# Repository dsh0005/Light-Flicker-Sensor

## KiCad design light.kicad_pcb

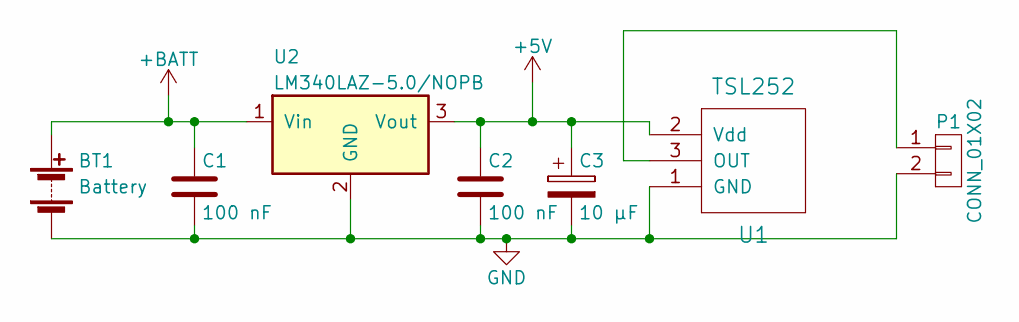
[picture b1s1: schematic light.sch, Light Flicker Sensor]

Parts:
BT1: Battery; TerminalBlock_bornier-2_P5.08mm
C1, C2: 100 nF; C_Disc_D5.0mm_W2.5mm_P5.00mm
C3: 10 µF; CP_Radial_Tantal_D5.0mm_P5.00mm
P1: CONN_01X02; TerminalBlock_bornier-2_P5.08mm
U1: TSL252; Pin_Header_Straight_1x03_Pitch2.00mm
U2: LM340LAZ-5.0/NOPB; TO-92_Inline_Narrow_Flip

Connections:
+5V: C2.1, C3.1, U1.2 (Vdd), U2.3 (Vout)
+BATT: BT1.1 (+), C1.1, U2.1 (Vin)
GND: BT1.2 (-), C1.2, C2.2, C3.2, P1.2, U1.1 (GND), U2.2 (GND)
unnamed: P1.1, U1.3 (OUT)

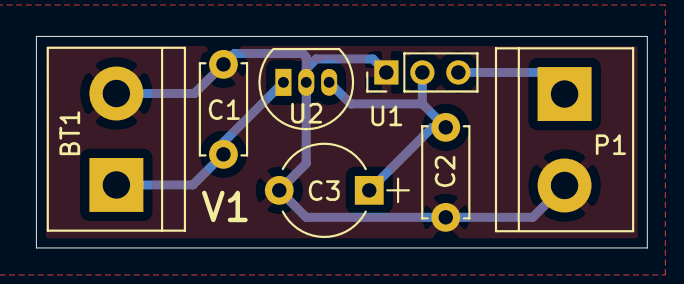
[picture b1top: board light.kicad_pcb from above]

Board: 2 copper layers, 33.9 x 11.8 mm, 7 parts (0 on the bottom side), 4 nets.

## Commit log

2017-10-08 Initial project.
2017-10-08 Schematic & footprint should be done.
2017-10-08 Should be good now.
2017-11-07 Change some footprints and the regulator.
2017-11-07 Issue date.
2017-11-10 Board V1 should be done. Ready for fab?
2017-11-10 Add LICENSE and README.
